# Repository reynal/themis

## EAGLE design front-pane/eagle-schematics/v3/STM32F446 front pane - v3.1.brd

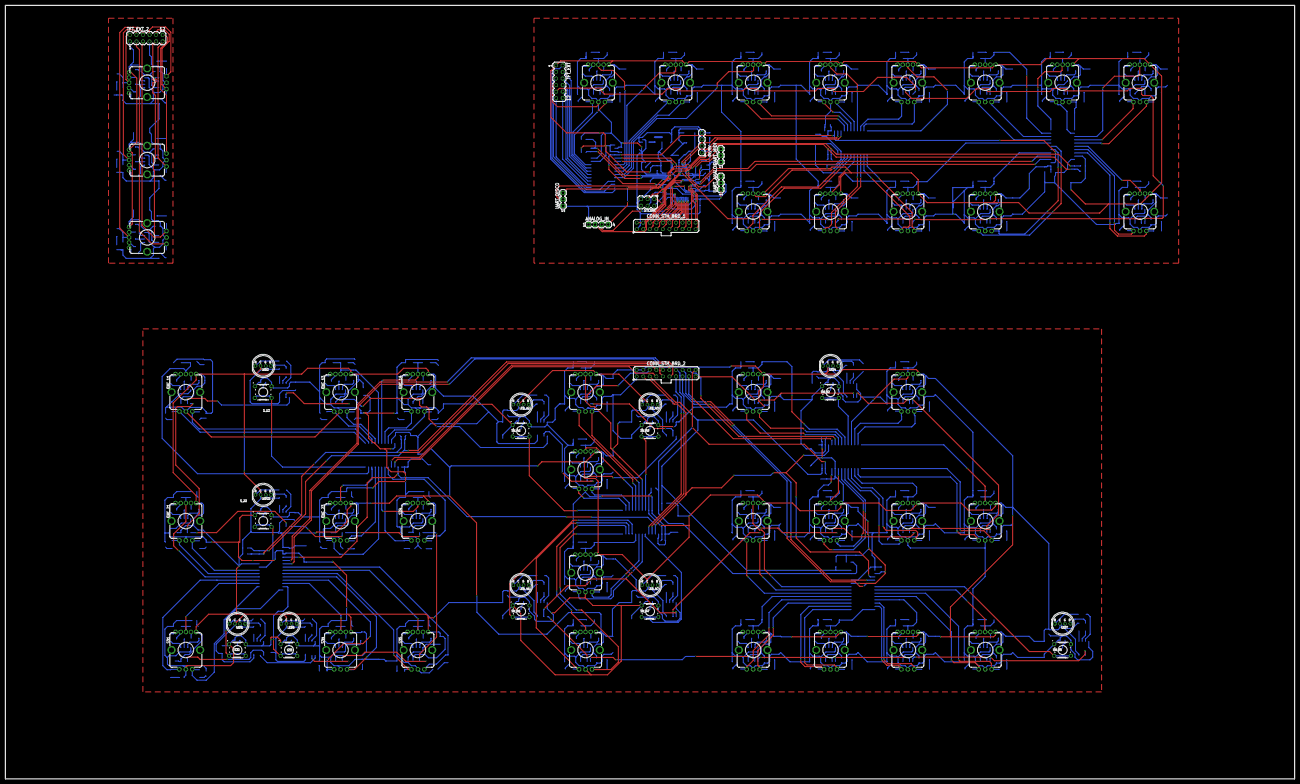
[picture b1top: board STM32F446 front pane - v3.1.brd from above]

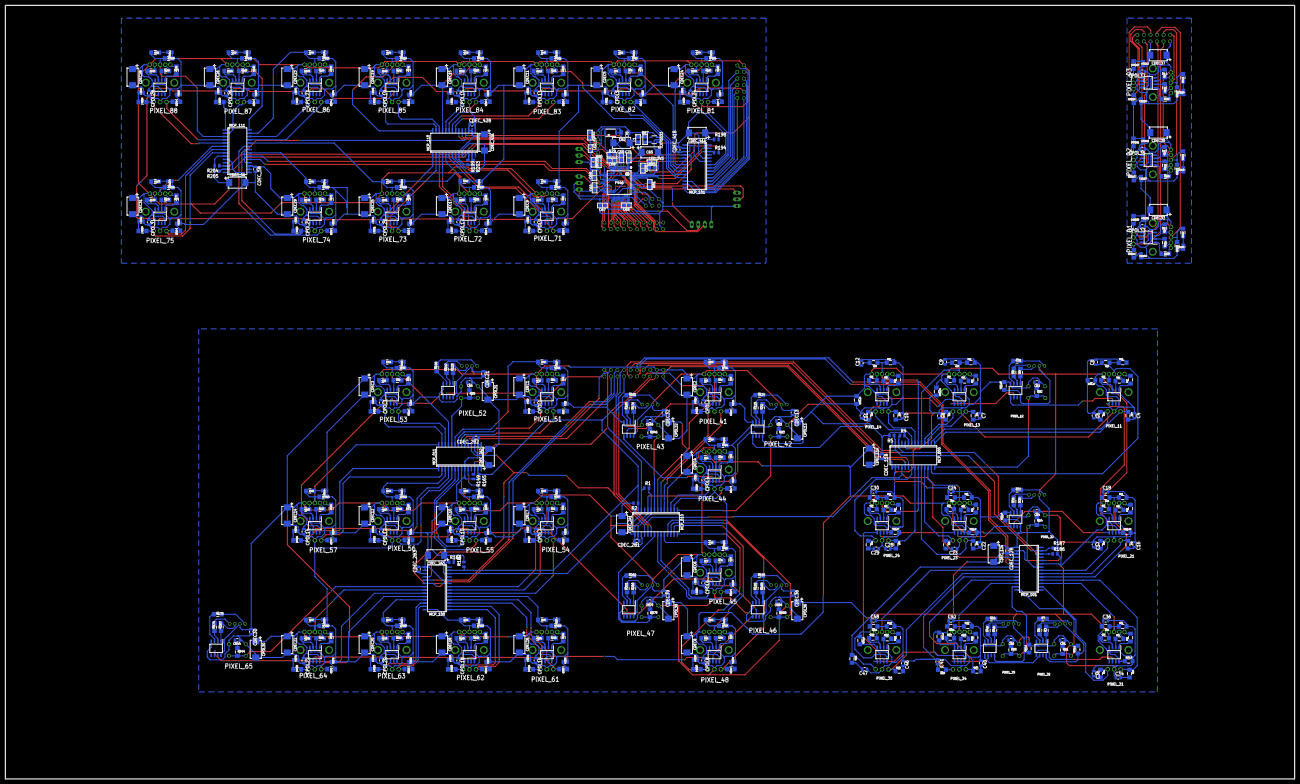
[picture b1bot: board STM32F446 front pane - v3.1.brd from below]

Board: 2 copper layers, 500.0 x 300.0 mm, 707 parts (638 on the bottom side), 663 nets.

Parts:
0V/5V: MA04-1
ANALOG_IN: MA04-1
C4, C5, C6, C7, C8, C9, C10, C11, C12, C16, C17, C18, C22, C23, C24, C28, C29, C30, C34, C35, C36, C40, C41, C42, C46, C47, C48: 10n; 0805-CAP
C55, C66, C67, C68, C69, C70: 0.1uF; C0805
C60: 2.2uF; C0805
C62: 10u; CPOL2917
C65: 100 uF; CPOL2917
C71: 1.0uF; C0805
C76: 1u; C1206
CB1, CB2, CB3, CB4, CB5, CB6, CB8, CB9, CB10, CB11, CB12, CB13, CB14, CB15, CB16, CB17, CB18, CB19, CB20, CB21, CB22, CB23, CB24, CB25, CB26, CB27, CB28, CB29, CB30, CB31, CB32, CB33, CB34, CB35, CB36, CB37, CB38, CB39, CB40, CB41, CB42, CB43, CB44, CB45, CB47, CB48, CB49, CB50, CB51, CB52, CB53, CB54, CB55, CB56, CB57, CB58, CB59, CB60, CB61, CB62, CB63, CB64, CB65, CB66, CB67, CB68, CB70, CB71, CB72, CB73, CB74, CB75, CB76, CB77, CB78, CB79, CB80, CB81, CB82, CB83, CB84, CB85, CB89, CB90, CB91, CB92, CB93, CB94, CB98, CB99, CB100, CB104, CB105, CB106, CB110, CB111, CB112, CB116, CB117, CB118: 10n; 0805-CAP
CDEC1, CDEC2, CDEC3, CDEC4, CDEC5, CDEC6, CDEC7, CDEC8, CDEC9, CDEC10, CDEC11, CDEC12, CDEC14, CDEC15, CDEC16, CDEC17, CDEC18, CDEC19, CDEC20, CDEC22, CDEC23, CDEC24, CDEC25, CDEC26, CDEC28, CDEC29, CDEC31, CDEC33, CDEC35, CDEC37: 10u; CPOL2917
CDEC13, CDEC21, CDEC30, CDEC32, CDEC36, CDEC39: 100n; 0805-CAP
CDEC_1, CDEC_2, CDEC_3, CDEC_4, CDEC_5, CDEC_6, CDEC_7, CDEC_8, CDEC_9, CDEC_10, CDEC_11, CDEC_12, CDEC_13: 100n; 1206
CDEC_2A1, CDEC_2A2, CDEC_2A3, CDEC_5A, CDEC_11A, CDEC_12A, CDEC_41A, CDEC_42A: 10u; CPOL2917
CDEC_2B1, CDEC_2B2, CDEC_2B3, CDEC_5B, CDEC_11B, CDEC_12B, CDEC_41B, CDEC_42B: 100n; 0805-CAP
CONN_STH_BRD_1, CONN_STH_BRD_2: MA10-2
CPOL1, CPOL2, CPOL3, CPOL4, CPOL5, CPOL6, CPOL7, CPOL8, CPOL9, CPOL10, CPOL11, CPOL12, CPOL14, CPOL15, CPOL16, CPOL17, CPOL18, CPOL19, CPOL20, CPOL22, CPOL23, CPOL24, CPOL25, CPOL26, CPOL28, CPOL29, CPOL31, CPOL33, CPOL35, CPOL37: 100n; 0805-CAP
CPOL13, CPOL21, CPOL30, CPOL32, CPOL36, CPOL39: 10u; CPOL2917
ENC_01, ENC_02, ENC_3, ENC_11, ENC_13, ENC_14, ENC_21, ENC_23, ENC_41, ENC_44, ENC_45, ENC_48, ENC_51, ENC_53, ENC_54, ENC_55, ENC_56, ENC_57, ENC_61, ENC_62, ENC_63, ENC_64, ENC_71, ENC_72, ENC_73, ENC_74, ENC_75, ENC_81, ENC_82, ENC_83, ENC_84, ENC_85, ENC_86, ENC_87, ENC_88: ENCODER_LED_3
F446: STM32F446RCT7; QFP50P1200X1200X160-64N
GREEN: 0805-LED
L1: 1 uH; L0805
LED1, LED2, LED4, LED6, LED7, LED22: CZXR-80RGB03-A; LED4-2.0-D8.0MM
LED_3V3: 0805-LED
LED_5V: 0603-LED
LED_42, LED_43, LED_46, LED_47: CZXR-80RGB03-A; LED4-2.0-D8.0MM
MCP_000, MCP_001, MCP_010, MCP_011, MCP_100, MCP_101, MCP_110, MCP_111: MCP23017; SOIC-28
PIXEL_01, PIXEL_02, PIXEL_03, PIXEL_11, PIXEL_12, PIXEL_13, PIXEL_14, PIXEL_21, PIXEL_22, PIXEL_23, PIXEL_24, PIXEL_31, PIXEL_32, PIXEL_33, PIXEL_34, PIXEL_35, PIXEL_41, PIXEL_42, PIXEL_43, PIXEL_44, PIXEL_45, PIXEL_46, PIXEL_47, PIXEL_48, PIXEL_51, PIXEL_52, PIXEL_53, PIXEL_54, PIXEL_55, PIXEL_56, PIXEL_57, PIXEL_61, PIXEL_62, PIXEL_63, PIXEL_64, PIXEL_65, PIXEL_71, PIXEL_72, PIXEL_73, PIXEL_74, PIXEL_75, PIXEL_81, PIXEL_83, PIXEL_84, PIXEL_85, PIXEL_86, PIXEL_87, PIXEL_88: NEOPIXEL-TLC59731DR; SOIC127P600X175-8N
PIXE_82: NEOPIXEL-TLC59731DR; SOIC127P600X175-8N
R1, R2, R4, R5, R90, R95, R149, R165, R166, R182, R186, R187, R194, R198, R199, R203, R204, R205: 1k; R0805
R3, R6, R7, R8, R9, R10, R11, R12, R17, R18, R19, R24, R25, R26, R31, R32, R33, R34, R35, R36, R37, R38, R39, R40, R45, R46, R47, R48, R49, R50, R51, R52, R53, R54, R59, R60, R61, R62, R63, R64, R65, R66, R67, R68, R73, R74, R75, R76, R77, R78, R80, R82, R83, R84, R85, R86, R94, R96, R97, R98, R99, R100, R101, R102, R103, R104, R109, R110, R111, R112, R113, R114, R115, R116, R117, R118, R123, R124, R125, R126, R127, R128, R129, R130, R131, R132, R133, R134, R135, R136, R137, R138, R139, R140, R141, R142, R143, R144, R145, R146, R147, R148, R150, R151, R152, R153, R154, R155, R156, R157, R158, R159, R160, R161, R162, R163, R164, R167, R168, R169, R170, R171, R172, R173, R174, R175, R176, R177, R178, R179, R180, R181, R183, R184, R185, R188, R189, R190, R191, R192, R193, R195, R196, R197, R200, R201, R202: 100; 1206
R13, R20, R27, R41, R55, R69, R88, R105, R119: 10k; 1206
R14, R15, R16, R21, R22, R23, R28, R29, R30, R42, R43, R44, R56, R57, R58, R70, R71, R72, R89, R91, R93, R106, R107, R108, R120, R121, R122: 470; 1206
R79: 100k; R0805
R81: 10K; R0805
R87: 1; R0805
R92: 470; R0805
RB1, RB2, RB3, RB4, RB5, RB6, RB8, RB9, RB10, RB11, RB12, RB13, RB14, RB15, RB16, RB17, RB18, RB19, RB20, RB21, RB22, RB23, RB24, RB25, RB26, RB27, RB28, RB29, RB30, RB31, RB32, RB33, RB34, RB35, RB36, RB37, RB38, RB39, RB40, RB41, RB42, RB43, RB44, RB45, RB47, RB48, RB49, RB50, RB51, RB52, RB53, RB54, RB55, RB56, RB57, RB58, RB59, RB60, RB61, RB62, RB63, RB64, RB65, RB66, RB67, RB68, RB70, RB71, RB72, RB73, RB74, RB75, RB76, RB77, RB78, RB79, RB80, RB81, RB82, RB83, RB84, RB85, RB89, RB90, RB91, RB92, RB93, RB94, RB98, RB99, RB100, RB104, RB105, RB106, RB110, RB111, RB112, RB116, RB117, RB118: 470; 1206
RPD1, RPD2, RPD3, RPD4, RPD5, RPD6, RPD7, RPD8, RPD9, RPD10, RPD11, RPD12, RPD14, RPD15, RPD16, RPD17, RPD18, RPD19, RPD20, RPD22, RPD23, RPD24, RPD25, RPD26, RPD28, RPD29, RPD31, RPD33, RPD35, RPD37: 10k; 1206
S2: SWITCH-SKRKAEE020; SKRKAEE020
S24, S31, S34, S35: ENCODER_LED_3
S32, S33: B3F-1000
STLINK: 75867-331LF; MA03-2
SW_42, SW_43, SW_46, SW_47, SW_52, SW_65: B3F-1000
S_12, S_22: B3F-1000
TFT_EXT: MA06-2
TFT_EXT_2: MA06-2
TLV75533: TLV75533PDBVR; SOT95P280X145-5N
UART_ANALOG: MA03-1
UART_DISCO: MA03-1
UART_MIDI: MA03-1

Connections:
3V3: C65.+, C66.2, C67.2, C68.2, C69.2, C70.2, C71.2, CDEC1.+, CDEC2.+, CDEC3.+, CDEC4.+, CDEC5.+, CDEC6.+, CDEC7.+, CDEC8.+, CDEC9.+, CDEC10.+, CDEC11.+, CDEC12.+, CDEC13.1, CDEC14.+, CDEC15.+, CDEC16.+, CDEC17.+, CDEC18.+, CDEC19.+, CDEC20.+, CDEC21.1, CDEC22.+, CDEC23.+, CDEC24.+, CDEC25.+, CDEC26.+, CDEC28.+, CDEC29.+, CDEC30.1, CDEC31.+, CDEC32.1, CDEC33.+, CDEC35.+, CDEC36.1, CDEC37.+, CDEC39.1, CDEC_1.1, CDEC_2.1, CDEC_2A1.+, CDEC_2A2.+, CDEC_2A3.+, CDEC_2B1.1, CDEC_2B2.1, CDEC_2B3.1, CDEC_3.1, CDEC_4.1, CDEC_5.1, CDEC_5A.+, CDEC_5B.1, CDEC_6.1, CDEC_7.1, CDEC_8.1, CDEC_9.1, CDEC_10.1, CDEC_11.1, CDEC_11A.+, CDEC_11B.1, CDEC_12.1, CDEC_12A.+, CDEC_12B.1, CDEC_13.1, CDEC_41A.+, CDEC_41B.1, CDEC_42A.+, CDEC_42B.1, CONN_STH_BRD_1.2, CONN_STH_BRD_1.4, CONN_STH_BRD_2.2, CONN_STH_BRD_2.4, CPOL1.1, CPOL2.1, CPOL3.1, CPOL4.1, CPOL5.1, CPOL6.1, CPOL7.1, CPOL8.1, CPOL9.1, CPOL10.1, CPOL11.1, CPOL12.1, CPOL13.+, CPOL14.1, CPOL15.1, CPOL16.1, CPOL17.1, CPOL18.1, CPOL19.1, CPOL20.1, CPOL21.+, CPOL22.1, CPOL23.1, CPOL24.1, CPOL25.1, CPOL26.1, CPOL28.1, CPOL29.1, CPOL30.+, CPOL31.1, CPOL32.+, CPOL33.1, CPOL35.1, CPOL36.+, CPOL37.1, CPOL39.+, ENC_01.5, ENC_02.5, ENC_3.5, ENC_11.5, ENC_13.5, ENC_14.5, ENC_21.5, ENC_23.5, ENC_41.5, ENC_44.5, ENC_45.5, ENC_48.5, ENC_51.5, ENC_53.5, ENC_54.5, ENC_55.5, ENC_56.5, ENC_57.5, ENC_61.5, ENC_62.5, ENC_63.5, ENC_64.5, ENC_71.5, ENC_72.5, ENC_73.5, ENC_74.5, ENC_75.5, ENC_81.5, ENC_82.5, ENC_83.5, ENC_84.5, ENC_85.5, ENC_86.5, ENC_87.5, ENC_88.5, F446.1, F446.13, F446.19, F446.32, F446.48, F446.64, L1.2, LED1.2, LED2.2, LED4.2, LED6.2, LED7.2, LED22.2, LED_42.2, LED_43.2, LED_46.2, LED_47.2, MCP_000.9, MCP_001.9, MCP_001.15, MCP_010.9, MCP_010.16, MCP_011.9, MCP_011.15, MCP_011.16, MCP_100.9, MCP_100.17, MCP_101.9, MCP_101.15, MCP_101.17, MCP_110.9, MCP_110.16, MCP_110.17, MCP_111.9, MCP_111.15, MCP_111.16, MCP_111.17, PIXEL_01.8, PIXEL_02.8, PIXEL_03.8, PIXEL_11.8, PIXEL_12.8, PIXEL_13.8, PIXEL_14.8, PIXEL_21.8, PIXEL_22.8, PIXEL_23.8, PIXEL_24.8, PIXEL_31.8, PIXEL_32.8, PIXEL_33.8, PIXEL_34.8, PIXEL_35.8, PIXEL_41.8, PIXEL_42.8, PIXEL_43.8, PIXEL_44.8, PIXEL_45.8, PIXEL_46.8, PIXEL_47.8, PIXEL_48.8, PIXEL_51.8, PIXEL_52.8, PIXEL_53.8, PIXEL_54.8, PIXEL_55.8, PIXEL_56.8, PIXEL_57.8, PIXEL_61.8, PIXEL_62.8, PIXEL_63.8, PIXEL_64.8, PIXEL_65.8, PIXEL_71.8, PIXEL_72.8, PIXEL_73.8, PIXEL_74.8, PIXEL_75.8, PIXEL_81.8, PIXEL_83.8, PIXEL_84.8, PIXEL_85.8, PIXEL_86.8, PIXEL_87.8, PIXEL_88.8, PIXE_82.8, R1.2, R2.2, R4.2, R5.2, R79.1, R95.1, R149.2, R165.2, R166.2, R182.2, R186.2, R187.2, R194.2, R198.2, R199.2, R203.2, R204.2, R205.2, S24.5, S31.5, S34.5, S35.5, STLINK.1, TFT_EXT.1, TFT_EXT_2.1
5V: 0V/5V.3, 0V/5V.4, C62.+, C76.2, R92.1, TLV75533.1, TLV75533.3
ADC1_IN1: ANALOG_IN.4, F446.15
ADC1_IN4: ANALOG_IN.3, F446.20
ADC1_IN10: ANALOG_IN.2, F446.8
BOOT1: F446.60, R81.1
DATA_PIXEL11: PIXEL_11.5, PIXEL_21.6
DATA_PIXEL12: PIXEL_11.6, PIXEL_12.5
DATA_PIXEL13: PIXEL_12.6, PIXEL_13.5
DATA_PIXEL14: PIXEL_13.6, PIXEL_14.5
DATA_PIXEL21: PIXEL_21.5, PIXEL_22.6
DATA_PIXEL22: PIXEL_22.5, PIXEL_23.6
DATA_PIXEL23: PIXEL_23.5, PIXEL_24.6
DATA_PIXEL24: PIXEL_24.5, PIXEL_35.6
DATA_PIXEL32: PIXEL_31.6, PIXEL_32.5
DATA_PIXEL33: PIXEL_32.6, PIXEL_33.5
DATA_PIXEL34: PIXEL_33.6, PIXEL_34.5
DATA_PIXEL35: PIXEL_34.6, PIXEL_35.5
ENC_01_A: ENC_01.A, RB104.1, TFT_EXT_2.3
ENC_01_B: ENC_01.B, RB105.1, TFT_EXT_2.5
ENC_01_SW: ENC_01.3, RB106.1, RPD33.1, TFT_EXT_2.6
ENC_02_A: ENC_02.A, RB110.1, TFT_EXT_2.11
ENC_02_B: ENC_02.B, RB111.1, TFT_EXT_2.12
ENC_02_SW: ENC_02.3, RB112.1, RPD35.1, TFT_EXT_2.4
ENC_03_A: ENC_3.A, RB116.1, TFT_EXT_2.10
ENC_03_B: ENC_3.B, RB117.1, TFT_EXT_2.8
ENC_03_SW: ENC_3.3, RB118.1, RPD37.1, TFT_EXT_2.2
GND: 0V/5V.1, 0V/5V.2, ANALOG_IN.1, C4.1, C5.1, C6.2, C7.1, C8.1, C9.2, C10.1, C11.1, C12.2, C16.1, C17.1, C18.2, C22.1, C23.1, C24.2, C28.1, C29.1, C30.2, C34.1, C35.1, C36.2, C40.1, C41.1, C42.2, C46.1, C47.1, C48.2, C55.1, C60.1, C62.-, C65.-, C66.1, C67.1, C68.1, C69.1, C70.1, C71.1, C76.1, CB1.1, CB2.1, CB3.1, CB4.1, CB5.1, CB6.1, CB8.1, CB9.1, CB10.2, CB11.1, CB12.1, CB13.2, CB14.1, CB15.1, CB16.2, CB17.1, CB18.1, CB19.2, CB20.1, CB21.1, CB22.2, CB23.1, CB24.1, CB25.2, CB26.1, CB27.1, CB28.2, CB29.1, CB30.1, CB31.2, CB32.1, CB33.1, CB34.2, CB35.1, CB36.1, CB37.2, CB38.1, CB39.1, CB40.2, CB41.1, CB42.1, CB43.2, CB44.1, CB45.1, CB47.1, CB48.1, CB49.2, CB50.1, CB51.1, CB52.2, CB53.1, CB54.1, CB55.2, CB56.1, CB57.1, CB58.2, CB59.1, CB60.1, CB61.2, CB62.1, CB63.1, CB64.2, CB65.1, CB66.1, CB67.2, CB68.1, CB70.1, CB71.1, CB72.1, CB73.2, CB74.1, CB75.1, CB76.2, CB77.1, CB78.1, CB79.2, CB80.1, CB81.1, CB82.2, CB83.1, CB84.1, CB85.2, CB89.1, CB90.1, CB91.2, CB92.1, CB93.1, CB94.2, CB98.1, CB99.1, CB100.2, CB104.1, CB105.1, CB106.2, CB110.1, CB111.1, CB112.2, CB116.1, CB117.1, CB118.2, CDEC1.-, CDEC2.-, CDEC3.-, CDEC4.-, CDEC5.-, CDEC6.-, CDEC7.-, CDEC8.-, CDEC9.-, CDEC10.-, CDEC11.-, CDEC12.-, CDEC13.2, CDEC14.-, CDEC15.-, CDEC16.-, CDEC17.-, CDEC18.-, CDEC19.-, CDEC20.-, CDEC21.2, CDEC22.-, CDEC23.-, CDEC24.-, CDEC25.-, CDEC26.-, CDEC28.-, CDEC29.-, CDEC30.2, CDEC31.-, CDEC32.2, CDEC33.-, CDEC35.-, CDEC36.2, CDEC37.-, CDEC39.2, CDEC_1.2, CDEC_2.2, CDEC_2A1.-, CDEC_2A2.-, CDEC_2A3.-, CDEC_2B1.2, CDEC_2B2.2, CDEC_2B3.2, CDEC_3.2, CDEC_4.2, CDEC_5.2, CDEC_5A.-, CDEC_5B.2, CDEC_6.2, CDEC_7.2, CDEC_8.2, CDEC_9.2, CDEC_10.2, CDEC_11.2, CDEC_11A.-, CDEC_11B.2, CDEC_12.2, CDEC_12A.-, CDEC_12B.2, CDEC_13.2, CDEC_41A.-, CDEC_41B.2, CDEC_42A.-, CDEC_42B.2, CONN_STH_BRD_1.1, CONN_STH_BRD_2.1, CPOL1.2, CPOL2.2, CPOL3.2, CPOL4.2, CPOL5.2, CPOL6.2, CPOL7.2, CPOL8.2, CPOL9.2, CPOL10.2, CPOL11.2, CPOL12.2, CPOL13.-, CPOL14.2, CPOL15.2, CPOL16.2, CPOL17.2, CPOL18.2, CPOL19.2, CPOL20.2, CPOL21.-, CPOL22.2, CPOL23.2, CPOL24.2, CPOL25.2, CPOL26.2, CPOL28.2, CPOL29.2, CPOL30.-, CPOL31.2, CPOL32.-, CPOL33.2, CPOL35.2, CPOL36.-, CPOL37.2, CPOL39.-, ENC_01.C, ENC_02.C, ENC_3.C, ENC_11.C, ENC_13.C, ENC_14.C, ENC_21.C, ENC_23.C, ENC_41.C, ENC_44.C, ENC_45.C, ENC_48.C, ENC_51.C, ENC_53.C, ENC_54.C, ENC_55.C, ENC_56.C, ENC_57.C, ENC_61.C, ENC_62.C, ENC_63.C, ENC_64.C, ENC_71.C, ENC_72.C, ENC_73.C, ENC_74.C, ENC_75.C, ENC_81.C, ENC_82.C, ENC_83.C, ENC_84.C, ENC_85.C, ENC_86.C, ENC_87.C, ENC_88.C, F446.12, F446.18, F446.31, F446.47, F446.63, GREEN.C, LED_3V3.C, LED_5V.C, MCP_000.10, MCP_000.15, MCP_000.16, MCP_000.17, MCP_001.10, MCP_001.16, MCP_001.17, MCP_010.10, MCP_010.15, MCP_010.17, MCP_011.10, MCP_011.17, MCP_100.10, MCP_100.15, MCP_100.16, MCP_101.10, MCP_101.16, MCP_110.10, MCP_110.15, MCP_111.10, PIXEL_01.4, PIXEL_02.4, PIXEL_03.4, PIXEL_11.4, PIXEL_12.4, PIXEL_13.4, PIXEL_14.4, PIXEL_21.4, PIXEL_22.4, PIXEL_23.4, PIXEL_24.4, PIXEL_31.4, PIXEL_32.4, PIXEL_33.4, PIXEL_34.4, PIXEL_35.4, PIXEL_41.4, PIXEL_42.4, PIXEL_43.4, PIXEL_44.4, PIXEL_45.4, PIXEL_46.4, PIXEL_47.4, PIXEL_48.4, PIXEL_51.4, PIXEL_52.4, PIXEL_53.4, PIXEL_54.4, PIXEL_55.4, PIXEL_56.4, PIXEL_57.4, PIXEL_61.4, PIXEL_62.4, PIXEL_63.4, PIXEL_64.4, PIXEL_65.4, PIXEL_71.4, PIXEL_72.4, PIXEL_73.4, PIXEL_74.4, PIXEL_75.4, PIXEL_81.4, PIXEL_83.4, PIXEL_84.4, PIXEL_85.4, PIXEL_86.4, PIXEL_87.4, PIXEL_88.4, PIXE_82.4, R13.2, R20.2, R27.2, R41.2, R55.2, R69.2, R81.2, R88.2, R105.2, R119.2, RPD1.2, RPD2.2, RPD3.2, RPD4.2, RPD5.2, RPD6.2, RPD7.2, RPD8.2, RPD9.2, RPD10.2, RPD11.2, RPD12.2, RPD14.2, RPD15.2, RPD16.2, RPD17.2, RPD18.2, RPD19.2, RPD20.2, RPD22.2, RPD23.2, RPD24.2, RPD25.2, RPD26.2, RPD28.2, RPD29.2, RPD31.2, RPD33.2, RPD35.2, RPD37.2, S2.1, S24.C, S31.C, S32.1, S32.2, S33.1, S33.2, S34.C, S35.C, STLINK.5, SW_42.1, SW_42.2, SW_43.1, SW_43.2, SW_46.1, SW_46.2, SW_47.1, SW_47.2, SW_52.1, SW_52.2, SW_65.1, SW_65.2, S_12.1, S_12.2, S_22.1, S_22.2, TFT_EXT.7, TFT_EXT_2.7, TLV75533.2, UART_ANALOG.1, UART_DISCO.1, UART_MIDI.1
GPA0_2: MCP_010.21, RB70.1, SW_47.3, SW_47.4
GPA0_5: ENC_74.3, MCP_111.21, RB94.1, RPD29.1
GPA0_11: MCP_000.21, R71.1, S24.B
GPA0_12: MCP_001.21, R121.1, S35.B
GPA0_31: ENC_51.A, MCP_011.21, RB8.1
GPA0_32: MCP_100.21, RB44.1, SW_65.3, SW_65.4
GPA0_41: ENC_81.3, MCP_101.21, RB79.1, RPD24.1
GPA0_42: ENC_83.A, MCP_110.21, RB38.1
GPA1_2: ENC_45.A, MCP_010.22, RB23.1
GPA1_5: ENC_74.B, MCP_111.22, RB93.1
GPA1_11: MCP_000.22, R70.1, S24.A
GPA1_12: MCP_001.22, R119.1, R122.1, S35.3
GPA1_31: ENC_51.B, MCP_011.22, RB9.1
GPA1_32: ENC_64.3, MCP_100.22, RB73.1, RPD22.1
GPA1_41: ENC_82.3, MCP_101.22, RB22.1, RPD5.1
GPA1_42: ENC_83.B, MCP_110.22, RB39.1
GPA2_2: ENC_45.B, MCP_010.23, RB24.1
GPA2_5: ENC_74.A, MCP_111.23, RB92.1
GPA2_11: MCP_000.23, R69.1, R72.1, S24.3
GPA2_12: MCP_001.23, R120.1, S35.A
GPA2_31: ENC_51.3, MCP_011.23, RB10.1, RPD1.1
GPA2_32: ENC_64.B, MCP_100.23, RB72.1
GPA2_41: ENC_82.A, MCP_101.23, RB20.1
GPA2_42: ENC_84.A, MCP_110.23, RB50.1
GPA3_2: ENC_45.3, MCP_010.24, RB25.1, RPD6.1
GPA3_5: ENC_73.3, MCP_111.24, RB82.1, RPD25.1
GPA3_11: ENC_23.A, MCP_000.24, R56.1
GPA3_12: MCP_001.24, R107.1, S34.B
GPA3_31: MCP_011.24, RB5.1, SW_52.3, SW_52.4
GPA3_32: ENC_64.A, MCP_100.24, RB71.1
GPA3_41: ENC_82.B, MCP_101.24, RB21.1
GPA3_42: ENC_84.B, MCP_110.24, RB51.1
GPA4_2: MCP_010.25, RB68.1, SW_46.3, SW_46.4
GPA4_5: ENC_86.A, MCP_111.25, RB74.1
GPA4_11: ENC_23.B, MCP_000.25, R57.1
GPA4_12: MCP_001.25, R106.1, S34.A
GPA4_31: ENC_53.3, MCP_011.25, RB16.1, RPD3.1
GPA4_32: ENC_63.3, MCP_100.25, RB67.1, RPD20.1
GPA4_41: ENC_83.3, MCP_101.25, RB40.1, RPD11.1
GPA4_42: ENC_84.3, MCP_110.25, RB52.1, RPD15.1
GPA5_2: ENC_48.A, MCP_010.26, RB29.1
GPA5_5: ENC_86.B, MCP_111.26, RB75.1
GPA5_11: ENC_23.3, MCP_000.26, R55.1, R58.1
GPA5_12: MCP_001.26, R105.1, R108.1, S34.3
GPA5_31: ENC_53.A, MCP_011.26, RB14.1
GPA5_32: ENC_63.B, MCP_100.26, RB66.1
GPA5_41: MCP_101.26, TFT_EXT.5
GPA5_42: ENC_85.A, MCP_110.26, RB62.1
GPA6_2: ENC_48.3, MCP_010.27, RB31.1, RPD8.1
GPA6_5: ENC_86.3, MCP_111.27, RB76.1, RPD23.1
GPA6_11: ENC_11.3, MCP_000.27, R13.1, R16.1
GPA6_12: MCP_001.27, RB6.1, S33.3, S33.4
GPA6_31: ENC_53.B, MCP_011.27, RB15.1
GPA6_32: ENC_63.A, MCP_100.27, RB65.1
GPA6_41: MCP_101.27, TFT_EXT.3
GPA6_42: ENC_85.B, MCP_110.27, RB63.1
GPA7_2: ENC_48.B, MCP_010.28, RB30.1
GPA7_5: ENC_87.3, MCP_111.28, RB85.1, RPD26.1
GPA7_11: MCP_000.28, RB2.1, S_12.3, S_12.4
GPA7_12: MCP_001.28, RB1.1, S32.3, S32.4
GPA7_31: ENC_57.3, MCP_011.28, RB49.1, RPD14.1
GPA7_32: ENC_62.3, MCP_100.28, RB61.1, RPD18.1
GPA7_41: MCP_101.28, TFT_EXT.2
GPA7_42: ENC_85.3, MCP_110.28, RB64.1, RPD19.1
GPB0_2: MCP_010.1, RB3.1, SW_42.3, SW_42.4
GPB0_5: ENC_87.B, MCP_111.1, RB84.1
GPB0_11: ENC_11.A, MCP_000.1, R14.1
GPB0_31: ENC_57.B, MCP_011.1, RB48.1
GPB0_32: ENC_62.B, MCP_100.1, RB60.1
GPB0_41: MCP_101.1, TFT_EXT.11
GPB0_42: ENC_73.B, MCP_110.1, RB81.1
GPB1_2: ENC_44.A, MCP_010.2, RB17.1
GPB1_5: ENC_87.A, MCP_111.2, RB83.1
GPB1_11: ENC_11.B, MCP_000.2, R15.1
GPB1_12: MCP_001.2, R91.1, S31.B
GPB1_31: ENC_57.A, MCP_011.2, RB47.1
GPB1_32: ENC_62.A, MCP_100.2, RB59.1
GPB1_41: MCP_101.2, TFT_EXT.12
GPB1_42: ENC_73.A, MCP_110.2, RB80.1
GPB2_2: ENC_44.B, MCP_010.3, RB18.1
GPB2_5: ENC_88.3, MCP_111.3, RB91.1, RPD28.1
GPB2_11: ENC_13.A, MCP_000.3, R21.1
GPB2_12: MCP_001.3, R88.1, R93.1, S31.3
GPB2_31: ENC_56.3, MCP_011.3, RB43.1, RPD12.1
GPB2_32: ENC_61.B, MCP_100.3, RB54.1
GPB2_41: MCP_101.3, TFT_EXT.10
GPB2_42: ENC_72.B, MCP_110.3, RB57.1
GPB3_2: ENC_44.3, MCP_010.4, RB19.1, RPD4.1
GPB3_5: ENC_88.A, MCP_111.4, RB89.1
GPB3_11: ENC_13.B, MCP_000.4, R22.1
GPB3_12: MCP_001.4, R89.1, S31.A
GPB3_31: ENC_56.B, MCP_011.4, RB42.1
GPB3_32: ENC_61.A, MCP_100.4, RB53.1
GPB3_41: MCP_101.4, TFT_EXT.8
GPB3_42: ENC_72.A, MCP_110.4, RB56.1
GPB4_2: ENC_41.A, MCP_010.5, RB11.1
GPB4_5: ENC_88.B, MCP_111.5, RB90.1
GPB4_11: ENC_13.3, MCP_000.5, R20.1, R23.1
GPB4_12: ENC_21.3, MCP_001.5, R41.1, R44.1
GPB4_31: ENC_56.A, MCP_011.5, RB41.1
GPB4_32: ENC_61.3, MCP_100.5, RB55.1, RPD16.1
GPB4_41: MCP_101.5, TFT_EXT.6
GPB4_42: ENC_72.3, MCP_110.5, RB58.1, RPD17.1
GPB5_2: ENC_41.B, MCP_010.6, RB12.1
GPB5_5: ENC_75.3, MCP_111.6, RB100.1, RPD31.1
GPB5_11: ENC_14.3, MCP_000.6, R27.1, R30.1
GPB5_12: ENC_21.A, MCP_001.6, R42.1
GPB5_31: ENC_55.A, MCP_011.6, RB35.1
GPB5_32: ENC_54.A, MCP_100.6, RB26.1
GPB5_41: MCP_101.6, TFT_EXT.4
GPB5_42: ENC_71.B, MCP_110.6, RB33.1
GPB6_2: ENC_41.3, MCP_010.7, RB13.1, RPD2.1
GPB6_5: ENC_75.A, MCP_111.7, RB98.1
GPB6_11: ENC_14.A, MCP_000.7, R28.1
GPB6_12: ENC_21.B, MCP_001.7, R43.1
GPB6_31: ENC_55.B, MCP_011.7, RB36.1
GPB6_32: ENC_54.B, MCP_100.7, RB27.1
GPB6_41: ENC_81.A, MCP_101.7, RB77.1
GPB6_42: ENC_71.A, MCP_110.7, RB32.1
GPB7_2: MCP_010.8, RB45.1, SW_43.3, SW_43.4
GPB7_5: ENC_75.B, MCP_111.8, RB99.1
GPB7_11: ENC_14.B, MCP_000.8, R29.1
GPB7_12: MCP_001.8, RB4.1, S_22.3, S_22.4
GPB7_31: ENC_55.3, MCP_011.8, RB37.1, RPD10.1
GPB7_32: ENC_54.3, MCP_100.8, RB28.1, RPD7.1
GPB7_41: ENC_81.B, MCP_101.8, RB78.1
GPB7_42: ENC_71.3, MCP_110.8, RB34.1, RPD9.1
GPIO_EXTI0: F446.5, MCP_101.19
GPIO_EXTI1: CONN_STH_BRD_1.17, F446.27
GPIO_EXTI2: F446.10, MCP_110.19
GPIO_EXTI3: F446.11, MCP_110.20
GPIO_EXTI4: F446.24, MCP_111.20
GPIO_EXTI5: F446.25, MCP_111.19
GPIO_EXTI6: CONN_STH_BRD_1.16, F446.37
GPIO_EXTI7: CONN_STH_BRD_1.13, F446.38
GPIO_EXTI8: CONN_STH_BRD_1.14, F446.39
GPIO_EXTI9: CONN_STH_BRD_1.9, F446.42
GPIO_EXTI10: CONN_STH_BRD_1.10, F446.43
GPIO_EXTI11: CONN_STH_BRD_1.7, F446.44
GPIO_EXTI12: CONN_STH_BRD_1.8, F446.45
GPIO_EXTI13: F446.2, MCP_101.20
GPIO_EXTI14: CONN_STH_BRD_1.18, F446.35
GPIO_EXTI15: CONN_STH_BRD_1.15, F446.36
I2C1_SCL: F446.61, MCP_101.12, MCP_110.12, MCP_111.12, R194.1, R199.1, R204.1
I2C1_SDA: F446.62, MCP_101.13, MCP_110.13, MCP_111.13, R198.1, R203.1, R205.1
I2C2_SCL: CONN_STH_BRD_1.20, CONN_STH_BRD_2.20, F446.29, MCP_010.12, MCP_011.12, MCP_100.12, R1.1, R149.1, R166.1
I2C2_SDA: CONN_STH_BRD_1.5, CONN_STH_BRD_2.5, F446.53, MCP_010.13, MCP_011.13, MCP_100.13, R2.1, R165.1, R182.1
I2C3_SCL: CONN_STH_BRD_1.12, CONN_STH_BRD_2.12, F446.41, MCP_000.12, MCP_001.12, R4.1, R186.1
I2C3_SDA: CONN_STH_BRD_1.11, CONN_STH_BRD_2.11, F446.40, MCP_000.13, MCP_001.13, R5.1, R187.1
INTA_2: CONN_STH_BRD_2.13, MCP_010.20
INTA_11: CONN_STH_BRD_2.8, MCP_000.20
INTA_12: CONN_STH_BRD_2.9, MCP_001.20
INTA_31: CONN_STH_BRD_2.18, MCP_011.20
INTA_32: CONN_STH_BRD_2.15, MCP_100.20
INTB_2: CONN_STH_BRD_2.14, MCP_010.19
INTB_11: CONN_STH_BRD_2.7, MCP_000.19
INTB_12: CONN_STH_BRD_2.10, MCP_001.19
INTB_31: CONN_STH_BRD_2.17, MCP_011.19
INTB_32: CONN_STH_BRD_2.16, MCP_100.19
unnamed: LED_5V.A, R92.2
unnamed: GREEN.A, R90.2
unnamed: LED_3V3.A, R95.2
unnamed: R87.2, TLV75533.5
unnamed: L1.1, R87.1
unnamed: PIXEL_42.1, R32.1
unnamed: PIXEL_32.1, R3.1
unnamed: PIXEL_32.2, R6.1
unnamed: ENC_11.1, R10.2
unnamed: ENC_11.2, R11.2
unnamed: ENC_11.4, R12.2
unnamed: PIXEL_11.1, R10.1
unnamed: PIXEL_11.2, R11.1
unnamed: PIXEL_11.3, R12.1
unnamed: C4.2, R14.2
unnamed: C5.2, R15.2
unnamed: C6.1, R16.2
unnamed: ENC_13.1, R17.2
unnamed: ENC_13.2, R18.2
unnamed: ENC_13.4, R19.2
unnamed: PIXEL_13.1, R17.1
unnamed: PIXEL_13.2, R18.1
unnamed: PIXEL_13.3, R19.1
unnamed: C7.2, R21.2
unnamed: C8.2, R22.2
unnamed: C9.1, R23.2
unnamed: ENC_14.1, R24.2
unnamed: ENC_14.2, R25.2
unnamed: ENC_14.4, R26.2
unnamed: PIXEL_14.1, R24.1
unnamed: PIXEL_14.2, R25.1
unnamed: PIXEL_14.3, R26.1
unnamed: C10.2, R28.2
unnamed: C11.2, R29.2
unnamed: C12.1, R30.2
unnamed: PIXEL_32.3, R7.1
unnamed: CB1.2, RB1.2
unnamed: LED1.1, R7.2
unnamed: LED1.4, R6.2
unnamed: LED1.3, R3.2
unnamed: PIXEL_12.1, R8.1
unnamed: PIXEL_12.2, R9.1
unnamed: PIXEL_12.3, R31.1
unnamed: CB2.2, RB2.2
unnamed: ENC_21.1, R38.2
unnamed: ENC_21.2, R39.2
unnamed: ENC_21.4, R40.2
unnamed: PIXEL_21.1, R38.1
unnamed: PIXEL_21.2, R39.1
unnamed: PIXEL_21.3, R40.1
unnamed: C16.2, R42.2
unnamed: C17.2, R43.2
unnamed: C18.1, R44.2
unnamed: LED2.1, R31.2
unnamed: LED2.4, R9.2
unnamed: LED2.3, R8.2
unnamed: PIXEL_42.2, R123.1
unnamed: ENC_51.1, R33.2
unnamed: ENC_51.2, R34.2
unnamed: ENC_51.4, R45.2
unnamed: PIXEL_51.1, R33.1
unnamed: PIXEL_51.2, R34.1
unnamed: ENC_23.1, R52.2
unnamed: ENC_23.2, R53.2
unnamed: ENC_23.4, R54.2
unnamed: PIXEL_23.1, R52.1
unnamed: PIXEL_23.2, R53.1
unnamed: PIXEL_23.3, R54.1
unnamed: C22.2, R56.2
unnamed: C23.2, R57.2
unnamed: C24.1, R58.2
unnamed: PIXEL_51.3, R45.1
unnamed: CB8.2, RB8.2
unnamed: CB9.2, RB9.2
unnamed: CB10.1, RB10.2
unnamed: PIXEL_22.1, R35.1
unnamed: PIXEL_22.2, R36.1
unnamed: PIXEL_22.3, R37.1
unnamed: CB4.2, RB4.2
unnamed: LED22.1, R37.2
unnamed: LED22.4, R36.2
unnamed: LED22.3, R35.2
unnamed: R66.2, S24.1
unnamed: R67.2, S24.2
unnamed: R68.2, S24.4
unnamed: PIXEL_24.1, R66.1
unnamed: PIXEL_24.2, R67.1
unnamed: PIXEL_24.3, R68.1
unnamed: C28.2, R70.2
unnamed: C29.2, R71.2
unnamed: C30.1, R72.2
unnamed: ENC_41.1, R46.2
unnamed: ENC_41.2, R47.2
unnamed: ENC_41.4, R51.2
unnamed: PIXEL_41.1, R46.1
unnamed: PIXEL_41.2, R47.1
unnamed: PIXEL_41.3, R51.1
unnamed: CB11.2, RB11.2
unnamed: R82.2, S31.1
unnamed: R84.2, S31.2
unnamed: R85.2, S31.4
unnamed: PIXEL_31.1, R82.1
unnamed: PIXEL_31.2, R84.1
unnamed: PIXEL_31.3, R85.1
unnamed: C34.2, R89.2
unnamed: C35.2, R91.2
unnamed: C36.1, R93.2
unnamed: CB12.2, RB12.2
unnamed: CB13.1, RB13.2
unnamed: PIXEL_33.1, R48.1
unnamed: PIXEL_33.2, R49.1
unnamed: PIXEL_33.3, R50.1
unnamed: CB6.2, RB6.2
unnamed: LED6.1, R50.2
unnamed: LED6.4, R49.2
unnamed: LED6.3, R48.2
unnamed: R102.2, S34.1
unnamed: R103.2, S34.2
unnamed: R104.2, S34.4
unnamed: PIXEL_34.1, R102.1
unnamed: PIXEL_34.2, R103.1
unnamed: PIXEL_34.3, R104.1
unnamed: C40.2, R106.2
unnamed: C41.2, R107.2
unnamed: C42.1, R108.2
unnamed: ENC_53.1, R59.2
unnamed: ENC_53.2, R60.2
unnamed: ENC_53.4, R61.2
unnamed: PIXEL_53.1, R59.1
unnamed: PIXEL_53.2, R60.1
unnamed: PIXEL_53.3, R61.1
unnamed: CB14.2, RB14.2
unnamed: CB15.2, RB15.2
unnamed: CB16.1, RB16.2
unnamed: R116.2, S35.1
unnamed: R117.2, S35.2
unnamed: R118.2, S35.4
unnamed: PIXEL_35.1, R116.1
unnamed: PIXEL_35.2, R117.1
unnamed: PIXEL_35.3, R118.1
unnamed: C46.2, R120.2
unnamed: C47.2, R121.2
unnamed: C48.1, R122.2
unnamed: ENC_44.1, R62.2
unnamed: ENC_44.2, R63.2
unnamed: ENC_44.4, R64.2
unnamed: PIXEL_44.1, R62.1
unnamed: PIXEL_44.2, R63.1
unnamed: PIXEL_44.3, R64.1
unnamed: CB17.2, RB17.2
unnamed: CB18.2, RB18.2
unnamed: CB19.1, RB19.2
unnamed: ENC_82.1, R65.2
unnamed: ENC_82.2, R73.2
unnamed: ENC_82.4, R74.2
unnamed: PIXE_82.1, R65.1
unnamed: PIXE_82.2, R73.1
unnamed: PIXE_82.3, R74.1
unnamed: CB20.2, RB20.2
unnamed: CB21.2, RB21.2
unnamed: CB22.1, RB22.2
unnamed: ENC_45.1, R75.2
unnamed: ENC_45.2, R76.2
unnamed: ENC_45.4, R77.2
unnamed: PIXEL_45.1, R75.1
unnamed: PIXEL_45.2, R76.1
unnamed: PIXEL_45.3, R77.1
unnamed: CB23.2, RB23.2
unnamed: CB24.2, RB24.2
unnamed: CB25.1, RB25.2
unnamed: ENC_54.1, R78.2
unnamed: ENC_54.2, R80.2
unnamed: ENC_54.4, R83.2
unnamed: PIXEL_54.1, R78.1
unnamed: PIXEL_54.2, R80.1
unnamed: PIXEL_54.3, R83.1
unnamed: CB26.2, RB26.2
unnamed: CB27.2, RB27.2
unnamed: CB28.1, RB28.2
unnamed: ENC_48.1, R86.2
unnamed: ENC_48.2, R94.2
unnamed: ENC_48.4, R96.2
unnamed: PIXEL_48.1, R86.1
unnamed: PIXEL_48.2, R94.1
unnamed: PIXEL_48.3, R96.1
unnamed: CB29.2, RB29.2
unnamed: CB30.2, RB30.2
unnamed: CB31.1, RB31.2
unnamed: ENC_71.1, R97.2
unnamed: ENC_71.2, R98.2
unnamed: ENC_71.4, R99.2
unnamed: PIXEL_71.1, R97.1
unnamed: PIXEL_71.2, R98.1
unnamed: PIXEL_71.3, R99.1
unnamed: CB32.2, RB32.2
unnamed: CB33.2, RB33.2
unnamed: CB34.1, RB34.2
unnamed: ENC_55.1, R100.2
unnamed: ENC_55.2, R101.2
unnamed: ENC_55.4, R109.2
unnamed: PIXEL_55.1, R100.1
unnamed: PIXEL_55.2, R101.1
unnamed: PIXEL_55.3, R109.1
unnamed: CB35.2, RB35.2
unnamed: CB36.2, RB36.2
unnamed: CB37.1, RB37.2
unnamed: ENC_83.1, R110.2
unnamed: ENC_83.2, R111.2
unnamed: ENC_83.4, R112.2
unnamed: PIXEL_83.1, R110.1
unnamed: PIXEL_83.2, R111.1
unnamed: PIXEL_83.3, R112.1
unnamed: CB38.2, RB38.2
unnamed: CB39.2, RB39.2
unnamed: CB40.1, RB40.2
unnamed: ENC_56.1, R113.2
unnamed: ENC_56.2, R114.2
unnamed: ENC_56.4, R115.2
unnamed: PIXEL_56.1, R113.1
unnamed: PIXEL_56.2, R114.1
unnamed: PIXEL_56.3, R115.1
unnamed: CB41.2, RB41.2
unnamed: CB42.2, RB42.2
unnamed: CB43.1, RB43.2
unnamed: PIXEL_42.3, R124.1
unnamed: CB3.2, RB3.2
unnamed: LED_42.1, R124.2
unnamed: LED_42.4, R123.2
unnamed: LED_42.3, R32.2
unnamed: PIXEL_52.1, R125.1
unnamed: PIXEL_52.2, R147.1
unnamed: PIXEL_52.3, R148.1
unnamed: CB5.2, RB5.2
unnamed: ENC_57.1, R126.2
unnamed: ENC_57.2, R127.2
unnamed: ENC_57.4, R128.2
unnamed: PIXEL_57.1, R126.1
unnamed: PIXEL_57.2, R127.1
unnamed: PIXEL_57.3, R128.1
unnamed: CB47.2, RB47.2
unnamed: CB48.2, RB48.2
unnamed: CB49.1, RB49.2
unnamed: ENC_84.1, R129.2
unnamed: ENC_84.2, R130.2
unnamed: ENC_84.4, R131.2
unnamed: PIXEL_84.1, R129.1
unnamed: PIXEL_84.2, R130.1
unnamed: PIXEL_84.3, R131.1
unnamed: CB50.2, RB50.2
unnamed: CB51.2, RB51.2
unnamed: CB52.1, RB52.2
unnamed: ENC_61.1, R132.2
unnamed: ENC_61.2, R133.2
unnamed: ENC_61.4, R134.2
unnamed: PIXEL_61.1, R132.1
unnamed: PIXEL_61.2, R133.1
unnamed: PIXEL_61.3, R134.1
unnamed: CB53.2, RB53.2
unnamed: CB54.2, RB54.2
unnamed: CB55.1, RB55.2
unnamed: ENC_72.1, R135.2
unnamed: ENC_72.2, R136.2
unnamed: ENC_72.4, R137.2
unnamed: PIXEL_72.1, R135.1
unnamed: PIXEL_72.2, R136.1
unnamed: PIXEL_72.3, R137.1
unnamed: CB56.2, RB56.2
unnamed: CB57.2, RB57.2
unnamed: CB58.1, RB58.2
unnamed: ENC_62.1, R138.2
unnamed: ENC_62.2, R139.2
unnamed: ENC_62.4, R140.2
unnamed: PIXEL_62.1, R138.1
unnamed: PIXEL_62.2, R139.1
unnamed: PIXEL_62.3, R140.1
unnamed: CB59.2, RB59.2
unnamed: CB60.2, RB60.2
unnamed: CB61.1, RB61.2
unnamed: ENC_85.1, R141.2
unnamed: ENC_85.2, R142.2
unnamed: ENC_85.4, R143.2
unnamed: PIXEL_85.1, R141.1
unnamed: PIXEL_85.2, R142.1
unnamed: PIXEL_85.3, R143.1
unnamed: CB62.2, RB62.2
unnamed: CB63.2, RB63.2
unnamed: CB64.1, RB64.2
unnamed: ENC_63.1, R144.2
unnamed: ENC_63.2, R145.2
unnamed: ENC_63.4, R146.2
unnamed: PIXEL_63.1, R144.1
unnamed: PIXEL_63.2, R145.1
unnamed: PIXEL_63.3, R146.1
unnamed: CB65.2, RB65.2
unnamed: CB66.2, RB66.2
unnamed: CB67.1, RB67.2
unnamed: LED4.1, R148.2
unnamed: LED4.4, R147.2
unnamed: LED4.3, R125.2
unnamed: ENC_64.1, R150.2
unnamed: ENC_64.2, R151.2
unnamed: ENC_64.4, R152.2
unnamed: PIXEL_64.1, R150.1
unnamed: PIXEL_64.2, R151.1
unnamed: PIXEL_64.3, R152.1
unnamed: CB71.2, RB71.2
unnamed: CB72.2, RB72.2
unnamed: CB73.1, RB73.2
unnamed: ENC_86.1, R153.2
unnamed: ENC_86.2, R154.2
unnamed: ENC_86.4, R155.2
unnamed: PIXEL_86.1, R153.1
unnamed: PIXEL_86.2, R154.1
unnamed: PIXEL_86.3, R155.1
unnamed: CB74.2, RB74.2
unnamed: CB75.2, RB75.2
unnamed: CB76.1, RB76.2
unnamed: ENC_81.1, R156.2
unnamed: ENC_81.2, R157.2
unnamed: ENC_81.4, R158.2
unnamed: PIXEL_81.1, R156.1
unnamed: PIXEL_81.2, R157.1
unnamed: PIXEL_81.3, R158.1
unnamed: CB77.2, RB77.2
unnamed: CB78.2, RB78.2
unnamed: CB79.1, RB79.2
unnamed: ENC_73.1, R159.2
unnamed: ENC_73.2, R160.2
unnamed: ENC_73.4, R161.2
unnamed: PIXEL_73.1, R159.1
unnamed: PIXEL_73.2, R160.1
unnamed: PIXEL_73.3, R161.1
unnamed: CB80.2, RB80.2
unnamed: CB81.2, RB81.2
unnamed: CB82.1, RB82.2
unnamed: ENC_87.1, R162.2
unnamed: ENC_87.2, R163.2
unnamed: ENC_87.4, R164.2
unnamed: PIXEL_87.1, R162.1
unnamed: PIXEL_87.2, R163.1
unnamed: PIXEL_87.3, R164.1
unnamed: CB83.2, RB83.2
unnamed: CB84.2, RB84.2
unnamed: CB85.1, RB85.2
unnamed: PIXEL_65.1, R167.1
unnamed: PIXEL_65.2, R174.1
unnamed: PIXEL_65.3, R175.1
unnamed: CB44.2, RB44.2
unnamed: LED7.1, R175.2
unnamed: LED7.4, R174.2
unnamed: LED7.3, R167.2
unnamed: ENC_88.1, R168.2
unnamed: ENC_88.2, R169.2
unnamed: ENC_88.4, R170.2
unnamed: PIXEL_88.1, R168.1
unnamed: PIXEL_88.2, R169.1
unnamed: PIXEL_88.3, R170.1
unnamed: CB89.2, RB89.2
unnamed: CB90.2, RB90.2
unnamed: CB91.1, RB91.2
unnamed: ENC_74.1, R171.2
unnamed: ENC_74.2, R172.2
unnamed: ENC_74.4, R173.2
unnamed: PIXEL_74.1, R171.1
unnamed: PIXEL_74.2, R172.1
unnamed: PIXEL_74.3, R173.1
unnamed: CB92.2, RB92.2
unnamed: CB93.2, RB93.2
unnamed: CB94.1, RB94.2
unnamed: PIXEL_43.1, R176.1
unnamed: PIXEL_43.2, R180.1
unnamed: PIXEL_43.3, R181.1
unnamed: CB45.2, RB45.2
unnamed: LED_43.1, R181.2
unnamed: LED_43.4, R180.2
unnamed: LED_43.3, R176.2
unnamed: ENC_75.1, R177.2
unnamed: ENC_75.2, R178.2
unnamed: ENC_75.4, R179.2
unnamed: PIXEL_75.1, R177.1
unnamed: PIXEL_75.2, R178.1
unnamed: PIXEL_75.3, R179.1
unnamed: CB98.2, RB98.2
unnamed: CB99.2, RB99.2
unnamed: CB100.1, RB100.2
unnamed: ENC_01.1, R183.2
unnamed: ENC_01.2, R184.2
unnamed: ENC_01.4, R185.2
unnamed: PIXEL_01.1, R183.1
unnamed: PIXEL_01.2, R184.1
unnamed: PIXEL_01.3, R185.1
unnamed: CB104.2, RB104.2
unnamed: CB105.2, RB105.2
unnamed: CB106.1, RB106.2
unnamed: PIXEL_46.1, R188.1
unnamed: PIXEL_46.2, R192.1
unnamed: PIXEL_46.3, R193.1
unnamed: CB68.2, RB68.2
unnamed: LED_46.1, R193.2
unnamed: LED_46.4, R192.2
unnamed: LED_46.3, R188.2
unnamed: ENC_02.1, R189.2
unnamed: ENC_02.2, R190.2
unnamed: ENC_02.4, R191.2
unnamed: PIXEL_02.1, R189.1
unnamed: PIXEL_02.2, R190.1
unnamed: PIXEL_02.3, R191.1
unnamed: CB110.2, RB110.2
unnamed: CB111.2, RB111.2
unnamed: CB112.1, RB112.2
unnamed: ENC_3.1, R195.2
unnamed: ENC_3.2, R196.2
unnamed: ENC_3.4, R197.2
unnamed: PIXEL_03.1, R195.1
unnamed: PIXEL_03.2, R196.1
unnamed: PIXEL_03.3, R197.1
unnamed: CB116.2, RB116.2
unnamed: CB117.2, RB117.2
unnamed: CB118.1, RB118.2
unnamed: PIXEL_47.1, R200.1
unnamed: PIXEL_47.2, R201.1
unnamed: PIXEL_47.3, R202.1
unnamed: CB70.2, RB70.2
unnamed: LED_47.1, R202.2
unnamed: LED_47.4, R201.2
unnamed: LED_47.3, R200.2
NRST: C55.2, F446.7, R79.2, S2.2, STLINK.3
PIXEL41: PIXEL_41.5, PIXEL_43.6
PIXEL42: PIXEL_14.6, PIXEL_42.5
PIXEL43: PIXEL_43.5, PIXEL_44.6
PIXEL44: PIXEL_42.6, PIXEL_44.5
PIXEL_02: PIXEL_01.6, PIXEL_02.5
PIXEL_03: PIXEL_02.6, PIXEL_03.5
PIXEL_45: PIXEL_45.5, PIXEL_46.6
PIXEL_46: PIXEL_46.5, PIXEL_48.6
PIXEL_47: PIXEL_45.6, PIXEL_47.5
PIXEL_48: PIXEL_48.5, PIXEL_61.6
PIXEL_51: PIXEL_51.5, PIXEL_52.6
PIXEL_52: PIXEL_52.5, PIXEL_53.6
PIXEL_53: PIXEL_53.5, PIXEL_57.6
PIXEL_54: PIXEL_47.6, PIXEL_54.5
PIXEL_55: PIXEL_54.6, PIXEL_55.5
PIXEL_56: PIXEL_55.6, PIXEL_56.5
PIXEL_57: PIXEL_56.6, PIXEL_57.5
PIXEL_61: PIXEL_61.5, PIXEL_62.6
PIXEL_62: PIXEL_62.5, PIXEL_63.6
PIXEL_63: PIXEL_63.5, PIXEL_64.6
PIXEL_64: PIXEL_64.5, PIXEL_65.6
PIXEL_71: PIXEL_71.5, PIXEL_72.6
PIXEL_72: PIXEL_72.5, PIXEL_73.6
PIXEL_73: PIXEL_73.5, PIXEL_74.6
PIXEL_74: PIXEL_74.5, PIXEL_75.6
PIXEL_75: PIXEL_75.5, PIXEL_88.6
PIXEL_81: PIXEL_81.5, TFT_EXT.9
PIXEL_82: PIXEL_81.6, PIXE_82.5
PIXEL_83: PIXEL_83.5, PIXE_82.6
PIXEL_84: PIXEL_83.6, PIXEL_84.5
PIXEL_85: PIXEL_84.6, PIXEL_85.5
PIXEL_86: PIXEL_85.6, PIXEL_86.5
PIXEL_87: PIXEL_86.6, PIXEL_87.5
PIXEL_88: PIXEL_87.6, PIXEL_88.5
PIXEL_IN: PIXEL_03.6, TFT_EXT_2.9
RST: CONN_STH_BRD_1.3, CONN_STH_BRD_2.3, F446.55, MCP_000.18, MCP_001.18, MCP_010.18, MCP_011.18, MCP_100.18, MCP_101.18, MCP_110.18, MCP_111.18
SPI1_MOSI: CONN_STH_BRD_1.6, CONN_STH_BRD_2.6, F446.23, PIXEL_41.6
SPI2_MOSI: F446.9, PIXEL_71.6
SPI3_MOSI: CONN_STH_BRD_1.19, CONN_STH_BRD_2.19, F446.26, PIXEL_51.6
SWCLK: F446.49, STLINK.4
SWDIO: F446.46, STLINK.2
TIM3_CH1: F446.22, R90.1
UART4_RX: F446.52, UART_ANALOG.2
UART4_TX: F446.14, UART_ANALOG.3
USART1_RX: F446.59, UART_DISCO.2
USART1_TX: F446.58, UART_DISCO.3
USART2_RX: F446.17, UART_MIDI.2
USART2_TX: F446.16, UART_MIDI.3
VCAP1: C60.2, F446.30

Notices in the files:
front-pane/eagle-schematics/v3/STM32F446 front pane - v3.1.brd:
RAINBOW by SYD X. REY (c) 2022
